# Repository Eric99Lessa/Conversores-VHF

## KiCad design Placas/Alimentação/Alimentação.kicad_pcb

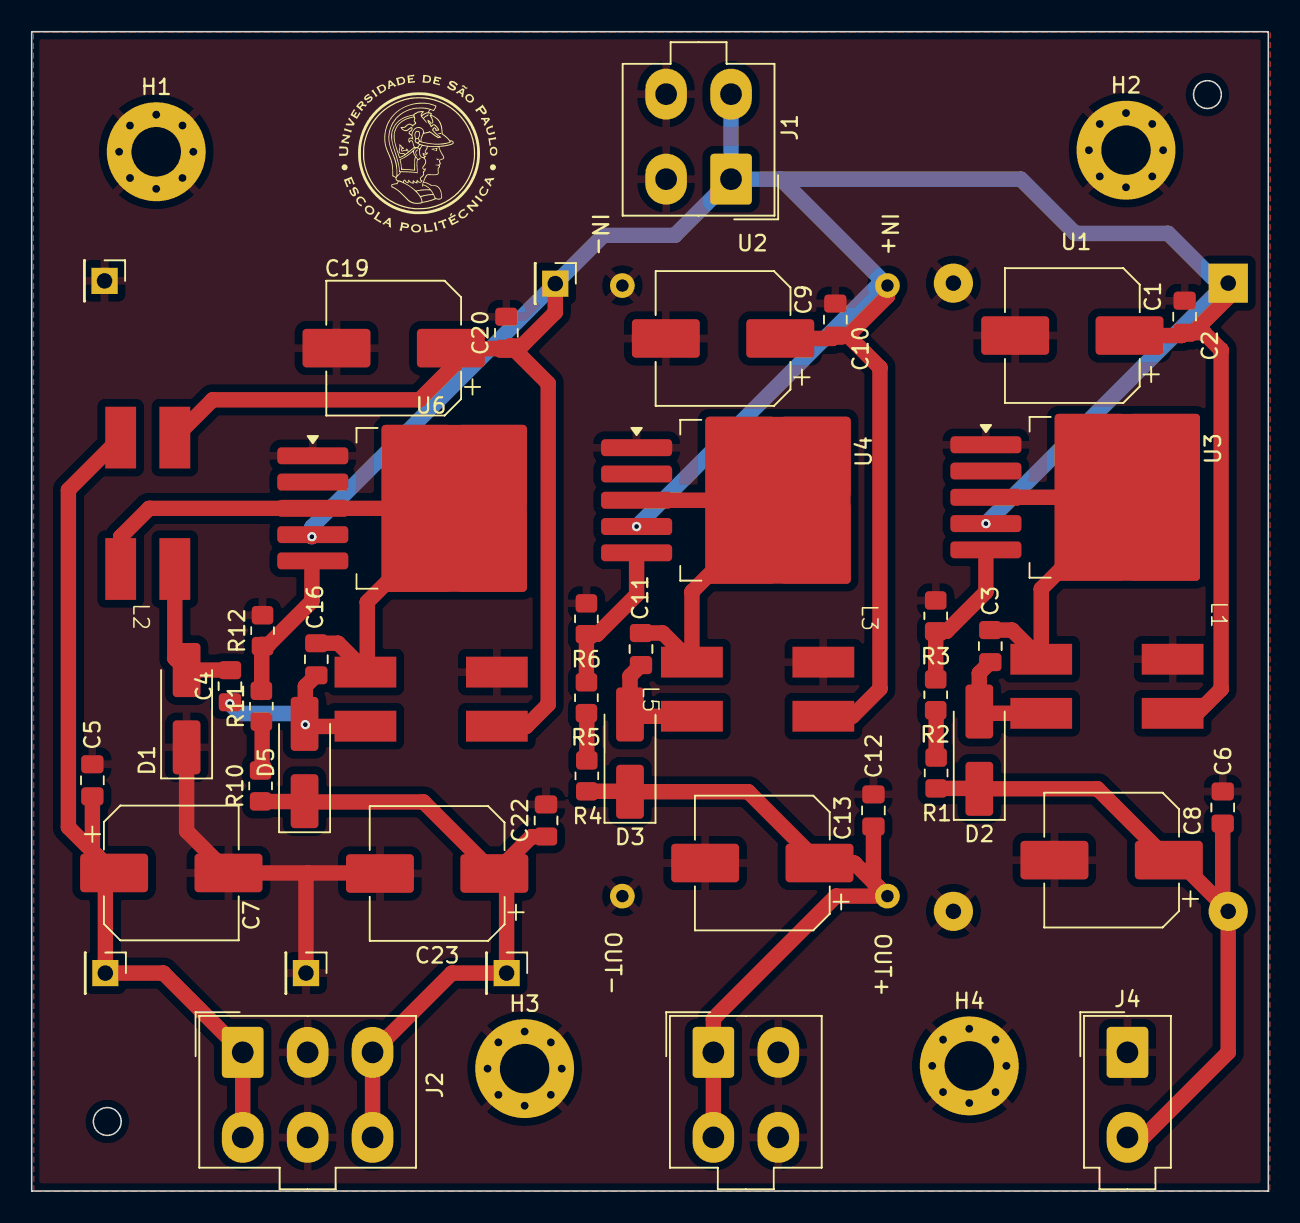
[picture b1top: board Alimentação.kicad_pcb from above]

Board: 2 copper layers, 80.0 x 75.0 mm, 53 parts (0 on the bottom side), 19 nets.

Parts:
C1, C7, C8, C9, C13, C19, C23: 220u; CP_Elec_8x10.5
C2, C5, C6, C10, C12, C20, C22: 1u; C_0805_2012Metric_Pad1.18x1.45mm_HandSolder
C3, C4, C11, C16: 22u; C_0805_2012Metric_Pad1.18x1.45mm_HandSolder
D1, D2, D3, D5: SS14; D_SMA_Handsoldering
H1, H2, H3, H4: MountingHole_Pad; MountingHole_3.2mm_M3_Pad_Via
J1, J3: Conn_02x02_ZigZag; Molex_Mini-Fit_Jr_5566-04A_2x02_P4.20mm_Vertical
J2: Conn_02x03_ZigZag; Molex_Mini-Fit_Jr_5566-06A_2x03_P4.20mm_Vertical
J4: Conn_02x01; Molex_Mini-Fit_Jr_5566-02A_2x01_P4.20mm_Vertical
J13, J14, J15, J16, J17: Conn_01x01_Pin; PinHeader_1x01_P2.54mm_Vertical
L1, L2, L3, L5: MSD1260t; Msd1260t
R1, R2: 1k5; R_0805_2012Metric_Pad1.20x1.40mm_HandSolder
R3, R5, R6, R11, R12: 1k; R_0805_2012Metric_Pad1.20x1.40mm_HandSolder
R4, R10: 10k; R_0805_2012Metric_Pad1.20x1.40mm_HandSolder
U1: YAAJ_DCDC_StepDown_LM2596
U2: Módulo XL6009; XL6009-Module
U3, U4, U6: XL6009; TO-263-5_TabPin3

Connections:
5V: C6.1, C8.1, D2.1 (K), J4.2, R1.1, U1.4 (Vout)
15V: C12.1, C13.1, D3.1 (K), J3.1, J3.3, R4.1, U2.3 (Vout)
+12V: C1.1, C2.1, C9.1, C10.1, C19.1, C20.1, J1.1, J1.3, J13.1, L1.1, L2.1, L3.1, L5.1, U1.1 (Vin), U2.1 (Vin), U3.4 (VIN), U4.4 (VIN), U6.4 (VIN)
+15V_sym: C22.1, C23.1, D5.1 (K), J2.3, J2.6, J17.1, R10.1
-15V_sym: C5.1, C7.1, J2.1, J2.4, J15.1, L2.2
/Conversor 12 to 5V/SEPIC_XL6011/L_out: C3.2, D2.2 (A), L1.4
/Conversor 12 to 5V/SEPIC_XL6011/SW: C3.1, L1.3, U3.3 (SW)
/Conversor 12 to 15V - Simétrico/L_out: C4.1, D5.2 (A), L5.4
/Conversor 12 to 15V - Simétrico/SW: L2.3, L5.3, U6.3 (SW)
/Conversor 12 to 15V/SEPIC_XL6012/L_out: C11.2, D3.2 (A), L3.4
/Conversor 12 to 15V/SEPIC_XL6012/SW: C11.1, L3.3, U4.3 (SW)
GND: C1.2, C2.2, C5.2, C6.2, C7.2, C8.2, C9.2, C10.2, C12.2, C13.2, C19.2, C20.2, C22.2, C23.2, D1.1 (K), H1.1, H2.1, H3.1, H4.1, J1.2, J1.4, J2.2, J2.5, J3.2, J3.4, J4.1, J14.1, J16.1, L1.2, L3.2, L5.2, R3.2, R6.2, R12.2, U1.2 (GND), U1.3 (GND), U2.2 (GND), U2.4 (GND), U3.1 (GND), U4.1 (GND), U6.1 (GND)
unnamed: C4.2, D1.2 (A), L2.4
unnamed: R1.2, R2.1
unnamed: R4.2, R5.1
unnamed: R10.2, R11.1
unnamed: R2.2, R3.1, U3.5 (FB)
unnamed: R5.2, R6.1, U4.5 (FB)
unnamed: R11.2, R12.1, U6.5 (FB)

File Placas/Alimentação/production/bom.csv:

Designator,Footprint,Quantity,Value,LCSC Part #
"C19, C23, C7",CP_Elec_8x10.5,3,220u,
"C20, C22, C5",0805,3,1u,
C4,0805,1,22u,
"D1, D5",D_SMA_Handsoldering,2,SS14,
"J1, J3",Molex_Mini-Fit_Jr_5566-04A_2x02_P4.20mm_Vertical,2,Conn_02x02_ZigZag,
J2,Molex_Mini-Fit_Jr_5566-06A_2x03_P4.20mm_Vertical,1,Conn_02x03_ZigZag,
J4,Molex_Mini-Fit_Jr_5566-02A_2x01_P4.20mm_Vertical,1,Conn_02x01,
"L2, L5",Msd1260t,2,MSD1260t,
R10,0805,1,10k,
"R11, R12",0805,2,1k,
U1,YAAJ_DCDC_StepDown_LM2596,1,YAAJ_DCDC_StepDown_LM2596,
U2,XL6009-Module,1,Módulo XL6009,
U6,TO-263-5_TabPin3,1,XL6009,

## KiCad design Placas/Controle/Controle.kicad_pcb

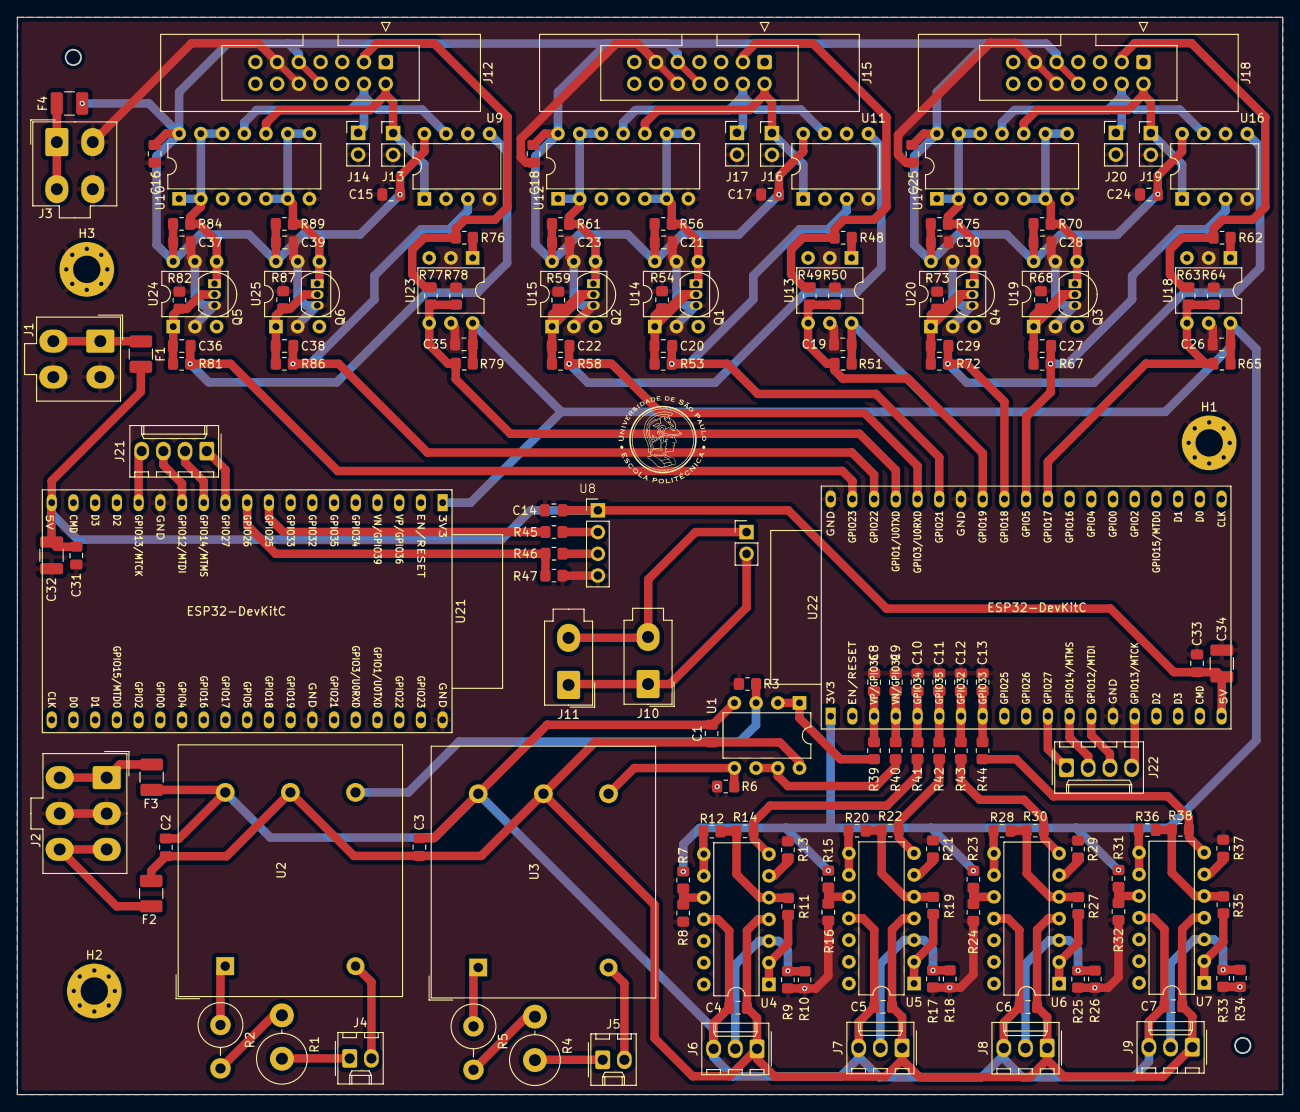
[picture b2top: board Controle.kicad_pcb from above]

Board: 2 copper layers, 148.0 x 126.0 mm, 176 parts (0 on the bottom side), 103 nets.

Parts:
C1, C2, C3, C4, C5, C6, C7, C14, C15, C16, C17, C18, C19, C21, C23, C24, C25, C26, C28, C30, C31, C33, C35, C37, C39: 0,1u; C_0805_2012Metric_Pad1.18x1.45mm_HandSolder
C8, C9, C10, C11, C12, C13: 330n; C_0805_2012Metric_Pad1.18x1.45mm_HandSolder
C20, C22, C27, C29, C36, C38: 6,8n; C_0805_2012Metric_Pad1.18x1.45mm_HandSolder
C32, C34: 10u; C_1210_3225Metric_Pad1.33x2.70mm_HandSolder
F1: 1A; Fuse_1210_3225Metric_Pad1.42x2.65mm_HandSolder
F2, F3: 0,4A; Fuse_1210_3225Metric_Pad1.42x2.65mm_HandSolder
F4: 3A; Fuse_1210_3225Metric_Pad1.42x2.65mm_HandSolder
H1, H2, H3: MountingHole_Pad; MountingHole_3.2mm_M3_Pad_Via
J1, J3: Conn_02x02; Molex_Mini-Fit_Jr_5566-04A_2x02_P4.20mm_Vertical
J2: Conn_02x03; Molex_Mini-Fit_Jr_5566-06A_2x03_P4.20mm_Vertical
J4, J5: Conn_01x02_Pin; Molex_KK-254_AE-6410-02A_1x02_P2.54mm_Vertical
J6, J7, J8, J9: Conn_01x03_Pin; Molex_KK-254_AE-6410-03A_1x03_P2.54mm_Vertical
J10, J11: Conn_01x02_Pin; Molex_Mini-Fit_Jr_5566-02A_2x01_P4.20mm_Vertical
J12, J15, J18: Conn_02x07_Odd_Even; IDC_Header_2x07
J13, J14, J16, J17, J19, J20: Conn_01x02_Pin; PinHeader_1x02_P2.54mm_Vertical
J21, J22: Conn_01x04_Pin; Molex_KK-254_AE-6410-04A_1x04_P2.54mm_Vertical
Q1, Q2, Q3, Q4, Q5, Q6: BC337; TO-92_Inline
R1: 3k3 1W; R_Axial_DIN0614_L14.3mm_D5.7mm_P5.08mm_Vertical
R2: 2k7 1W; R_Axial_DIN0516_L15.5mm_D5.0mm_P5.08mm_Vertical
R3, R6, R9, R10, R17, R18, R25, R26, R33, R34: 100 1/8W; R_0805_2012Metric_Pad1.20x1.40mm_HandSolder
R4: 4k7 2W; R_Axial_DIN0614_L14.3mm_D5.7mm_P5.08mm_Vertical
R5: 3k3 1/2W; R_Axial_DIN0516_L15.5mm_D5.0mm_P5.08mm_Vertical
R7, R8, R11, R12, R14, R15, R16, R19, R20, R22, R23, R24, R27, R28, R30, R31, R32, R35, R36, R38, R46: 10k; R_0805_2012Metric_Pad1.20x1.40mm_HandSolder
R13, R21, R29, R37, R50, R64, R78: 3k3; R_0805_2012Metric_Pad1.20x1.40mm_HandSolder
R39, R40, R41, R42, R43, R44, R51, R56, R61, R65, R70, R75, R79, R84, R89: 1k; R_0805_2012Metric_Pad1.20x1.40mm_HandSolder
R45: 100; R_0805_2012Metric_Pad1.20x1.40mm_HandSolder
R47: 20k; R_0805_2012Metric_Pad1.20x1.40mm_HandSolder
R48, R62, R76: 1k3; R_0805_2012Metric_Pad1.20x1.40mm_HandSolder
R49, R63, R77: 12k; R_0805_2012Metric_Pad1.20x1.40mm_HandSolder
R53, R58, R67, R72, R81, R86: 178; R_0805_2012Metric_Pad1.20x1.40mm_HandSolder
R54, R59, R68, R73, R82, R87: 100k; R_0805_2012Metric_Pad1.20x1.40mm_HandSolder
U1: LM358; DIP-8_W7.62mm
U2, U3: LV25-P; LEM_LV25-P
U4, U5, U6, U7: LM324; DIP-14_W7.62mm
U8: Módulo TJA1050; TJA1050
U9, U11, U16: TL072; DIP-8_W7.62mm
U10, U12, U17: HEF4093B; DIP-14_W7.62mm
U13, U14, U15, U18, U19, U20, U23, U24, U25: H11L1; DIP-6_W7.62mm
U21, U22: ESP32-DevKitC

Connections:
+3.3V: C19.1, C26.1, C35.1, R7.1, R15.1, R23.1, R31.1, R51.1, R65.1, R79.1, U13.6, U18.6, U21.1 (3V3), U22.1 (3V3), U23.6
+5V: C14.1, C31.1, C32.1, C33.1, C34.1, F1.2, U8.1 (VCC), U21.19 (5V), U22.19 (5V)
+15V: C1.1, C2.1, C3.1, C4.1, C5.1, C6.1, C7.1, F2.2, J6.1, J7.1, J8.1, J9.1, U1.8 (V+), U2.5 (V+), U3.5 (V+), U4.4 (V+), U5.4 (V+), U6.4 (V+), U7.4 (V+)
-15V: C1.2, C2.2, C3.2, C4.2, C5.2, C6.2, C7.2, F3.2, J6.3, J7.3, J8.3, J9.3, U1.4 (V-), U2.6 (V-), U3.6 (V-), U4.11 (V-), U5.11 (V-), U6.11 (V-), U7.11 (V-)
/Adequação Sensores/Filtro RC1/unfilt_signal: R40.1, U1.6 (-), U1.7
/Adequação Sensores/Filtro RC2/unfilt_signal: R14.1, R41.1, U4.7
/Adequação Sensores/Filtro RC3/unfilt_signal: R22.1, R42.1, U5.7
/Adequação Sensores/Filtro RC4/unfilt_signal: R30.1, R43.1, U6.7
/Adequação Sensores/Filtro RC5/unfilt_signal: R38.1, R44.1, U7.7
/Adequação Sensores/Filtro RC/unfilt_signal: R39.1, U1.1, U1.2 (-)
/Adequação Sensores/adequacao_sensor_tensao1/output_signal: R6.2, U1.5 (+), U3.4 (M)
/Adequação Sensores/adequacao_sensor_tensao/output_signal: R3.2, U1.3 (+), U2.4 (M)
/Adequação Sinais Driver/Conectores - PWM e erro1/Adequação Sinais - PWM1/in_si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: C20.2, Q1.2 (B), R53.2, R54.1, U14.1
/Adequação Sinais Driver/Conectores - PWM e erro1/Adequação Sinais - PWM/in_sig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: C22.2, Q2.2 (B), R58.2, R59.1, U15.1
/Adequação Sinais Driver/Conectores - PWM e erro1/PWM_BOT_driver: J15.2, J16.1, U11.1, U12.10
/Adequação Sinais Driver/Conectores - PWM e erro1/PWM_BOT_int: Q1.1 (C), R56.2, U12.5, U12.6, U12.8, U12.9, U14.4
/Adequação Sinais Driver/Conectores - PWM e erro1/PWM_TOP_driver: J15.4, J17.1, U11.7, U12.11
/Adequação Sinais Driver/Conectores - PWM e erro1/PWM_TOP_int: Q2.1 (C), R61.2, U12.1, U12.2, U12.12, U12.13, U15.4
/Adequação Sinais Driver/Conectores - PWM e erro1/erro_driver: J15.3, R48.1, R49.2
/Adequação Sinais Driver/Conectores - PWM e erro2/Adequação Sinais - PWM1/in_si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: C27.2, Q3.2 (B), R67.2, R68.1, U19.1
/Adequação Sinais Driver/Conectores - PWM e erro2/Adequação Sinais - PWM/in_sig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: C29.2, Q4.2 (B), R72.2, R73.1, U20.1
/Adequação Sinais Driver/Conectores - PWM e erro2/PWM_BOT_driver: J18.2, J19.1, U16.1, U17.10
/Adequação Sinais Driver/Conectores - PWM e erro2/PWM_BOT_int: Q3.1 (C), R70.2, U17.5, U17.6, U17.8, U17.9, U19.4
/Adequação Sinais Driver/Conectores - PWM e erro2/PWM_TOP_driver: J18.4, J20.1, U16.7, U17.11
/Adequação Sinais Driver/Conectores - PWM e erro2/PWM_TOP_int: Q4.1 (C), R75.2, U17.1, U17.2, U17.12, U17.13, U20.4
/Adequação Sinais Driver/Conectores - PWM e erro2/erro_driver: J18.3, R62.1, R63.2
/Adequação Sinais Driver/Conectores - PWM e erro/Adequação Sinais - PWM1/in_sig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: C38.2, Q6.2 (B), R86.2, R87.1, U25.1
/Adequação Sinais Driver/Conectores - PWM e erro/Adequação Sinais - PWM/in_sign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: C36.2, Q5.2 (B), R81.2, R82.1, U24.1
/Adequação Sinais Driver/Conectores - PWM e erro/PWM_BOT_driver: J12.2, J13.1, U9.1, U10.10
/Adequação Sinais Driver/Conectores - PWM e erro/PWM_BOT_int: Q6.1 (C), R89.2, U10.5, U10.6, U10.8, U10.9, U25.4
/Adequação Sinais Driver/Conectores - PWM e erro/PWM_TOP_driver: J12.4, J14.1, U9.7, U10.11
/Adequação Sinais Driver/Conectores - PWM e erro/PWM_TOP_int: Q5.1 (C), R84.2, U10.1, U10.2, U10.12, U10.13, U24.4
/Adequação Sinais Driver/Conectores - PWM e erro/erro_driver: J12.3, R76.1, R77.2
/Conectores/5V_conn: F1.1, J1.1, J1.3
/Conectores/+15V_sym_conn: F2.1, J2.3, J2.6
/Conectores/-15V_sym_conn: F3.1, J2.1, J2.4
/Conectores/Vdrive_conn: F4.1, J3.1, J3.3
/I_read_L1: C10.1, R41.2, U22.5 (VDET_1/GPIO34/ADC1_CH6)
/I_read_L2: C11.1, R42.2, U22.6 (VDET_2/GPIO35/ADC1_CH7)
/I_read_L3: C12.1, R43.2, U22.7 (32K_XP/GPIO32/ADC1_CH4)
/I_read_out: C13.1, R44.2, U22.8 (32K_XN/GPIO33/ADC1_CH5)
/Microcontrolados e CAN/CANH: J10.2, J11.2, U8.5 (CANH)
/Microcontrolados e CAN/CANL: J10.1, J11.1, U8.6 (CANL)
/Microcontrolados e CAN/CAN_RX_esp: R46.2, R47.1, U21.10 (DAC_2/ADC2_CH9/GPIO26)
/Microcontrolados e CAN/CAN_RX_trans: R46.1, U8.3 (RX)
/Microcontrolados e CAN/CAN_TX_esp: R45.2, U21.9 (DAC_1/ADC2_CH8/GPIO25)
/Microcontrolados e CAN/CAN_TX_trans: R45.1, U8.2 (TX)
/Microcontrolados e CAN/CS_1: J22.1, U22.11 (ADC2_CH7/GPIO27)
/Microcontrolados e CAN/CS_2: J21.1, U21.11 (ADC2_CH7/GPIO27)
/Microcontrolados e CAN/MISO_1: J22.3, U22.13 (MTDI/GPIO12/ADC2_CH5)
/Microcontrolados e CAN/MISO_2: J21.3, U21.13 (MTDI/GPIO12/ADC2_CH5)
/Microcontrolados e CAN/MOSI_1: J22.4, U22.15 (MTCK/GPIO13/ADC2_CH4)
/Microcontrolados e CAN/MOSI_2: J21.4, U21.15 (MTCK/GPIO13/ADC2_CH4)
/Microcontrolados e CAN/SCK_1: J22.2, U22.12 (MTMS/GPIO14/ADC2_CH6)
/Microcontrolados e CAN/SCK_2: J21.2, U21.12 (MTMS/GPIO14/ADC2_CH6)
/PWM_BOT_1: C38.1, R86.1, U9.3 (+), U22.36 (GPIO22)
/PWM_BOT_2: C20.1, R53.1, U11.3 (+), U22.33 (GPIO21)
/PWM_BOT_3: C29.1, R72.1, U16.5 (+), U22.30 (GPIO18)
/PWM_TOP_1: C36.1, R81.1, U9.5 (+), U22.37 (GPIO23)
/PWM_TOP_2: C22.1, R58.1, U11.5 (+), U22.34 (U0RXD/GPIO3)
/PWM_TOP_3: C27.1, R67.1, U16.3 (+), U22.29 (GPIO5)
/V_read_in: C8.1, R39.2, U22.3 (SENSOR_VP/GPIO36/ADC1_CH0)
/V_read_out: C9.1, R40.2, U22.4 (SENSOR_VN/GPIO39/ADC1_CH3)
/err_1: R77.1, R78.2, R79.2, U22.35 (U0TXD/GPIO1), U23.4
/err_2: R49.1, R50.2, R51.2, U13.4, U22.31 (GPIO19)
/err_3: R63.1, R64.2, R65.2, U18.4, U22.28 (GPIO17)
GND: C8.2, C9.2, C10.2, C11.2, C12.2, C13.2, C14.2, C15.2, C16.2, C17.2, C18.2, C19.2, C21.2, C23.2, C24.2, C25.2, C26.2, C28.2, C30.2, C31.2, C32.2, C33.2, C34.2, C35.2, C37.2, C39.2, H1.1, H2.1, H3.1, J1.2, J1.4, J2.2, J2.5, J3.2, J3.4, J12.10, J12.11, J13.2, J14.2, J15.10, J15.11, J16.2, J17.2, J18.10, J18.11, J19.2, J20.2, Q1.3 (E), Q2.3 (E), Q3.3 (E), Q4.3 (E), Q5.3 (E), Q6.3 (E), R3.1, R6.1, R8.2, R9.1, R10.1, R13.2, R16.2, R17.1, R18.1, R21.2, R24.2, R25.1, R26.1, R29.2, R32.2, R33.1, R34.1, R37.2, R47.2, R50.1, R54.2, R59.2, R64.1, R68.2, R73.2, R78.1, R82.2, R87.2, U8.4 (GND), U9.2 (-), U9.4 (V-), U9.6 (-), U10.7 (GND), U11.2 (-), U11.4 (V-), U11.6 (-), U12.7 (GND), U13.2, U13.5, U14.2, U14.5, U15.2, U15.5, U16.2 (-), U16.4 (V-), U16.6 (-), U17.7 (GND), U18.2, U18.5, U19.2, U19.5, U20.2, U20.5, U21.14 (GND), U21.32 (GND), U21.38 (GND), U22.14 (GND), U22.32 (GND), U22.38 (GND), U23.2, U23.5, U24.2, U24.5, U25.2, U25.5
unnamed: J4.1, R1.1
unnamed: J4.2, U2.3 (HV-)
unnamed: J5.1, R4.1
unnamed: J5.2, U3.3 (HV-)
unnamed: J6.2, R9.2, R10.2, U4.3 (+)
unnamed: J7.2, R17.2, R18.2, U5.3 (+)
unnamed: J8.2, R25.2, R26.2, U6.3 (+)
unnamed: J9.2, R33.2, R34.2, U7.3 (+)
unnamed: R1.2, R2.2
unnamed: R4.2, R5.2
unnamed: R48.2, U13.1
unnamed: R62.2, U18.1
unnamed: R76.2, U23.1
unnamed: R2.1, U2.1 (HV+)
unnamed: R5.1, U3.1 (HV+)
unnamed: R11.2, U4.1, U4.2 (-)
unnamed: R11.1, R12.1, R14.2, U4.5 (+)
unnamed: R13.1, U4.6 (-)
unnamed: R7.2, R8.1, U4.10 (+)
unnamed: R12.2, U4.8, U4.9 (-)
unnamed: R19.2, U5.1, U5.2 (-)
unnamed: R19.1, R20.1, R22.2, U5.5 (+)
unnamed: R21.1, U5.6 (-)
unnamed: R15.2, R16.1, U5.10 (+)
unnamed: R20.2, U5.8, U5.9 (-)
unnamed: R27.2, U6.1, U6.2 (-)
unnamed: R27.1, R28.1, R30.2, U6.5 (+)
unnamed: R29.1, U6.6 (-)
unnamed: R23.2, R24.1, U6.10 (+)
unnamed: R28.2, U6.8, U6.9 (-)
unnamed: R35.2, U7.1, U7.2 (-)
unnamed: R35.1, R36.1, R38.2, U7.5 (+)
unnamed: R37.1, U7.6 (-)
unnamed: R31.2, R32.1, U7.10 (+)
unnamed: R36.2, U7.8, U7.9 (-)
Vdrive: C15.1, C16.1, C17.1, C18.1, C21.1, C23.1, C24.1, C25.1, C28.1, C30.1, C37.1, C39.1, F4.2, J12.8, J12.9, J15.8, J15.9, J18.8, J18.9, R56.1, R61.1, R70.1, R75.1, R84.1, R89.1, U9.8 (V+), U10.14 (VCC), U11.8 (V+), U12.14 (VCC), U14.6, U15.6, U16.8 (V+), U17.14 (VCC), U19.6, U20.6, U24.6, U25.6

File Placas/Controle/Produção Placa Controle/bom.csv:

Designator,Footprint,Quantity,Value,LCSC Part #
"C1, C14, C15, C16, C17, C18, C19, C2, C21, C23, C24, C25, C26, C28, C3, C30, C31, C33, C35, C37, C39, C4, C5, C6, C7",0805,25,"0,1u",
"C10, C11, C12, C13, C8, C9",0805,6,330n,
"C20, C22, C27, C29, C36, C38",0805,6,"6,8n",
"C32, C34",1210,2,10u,
F1,1210,1,1A,
"F2, F3",1210,2,"0,4A",
F4,1210,1,3A,
"J1, J3",Molex_Mini-Fit_Jr_5566-04A_2x02_P4.20mm_Vertical,2,Conn_02x02,
"J10, J11",Molex_Mini-Fit_Jr_5566-02A_2x01_P4.20mm_Vertical,2,Conn_01x02_Pin,
"J12, J15, J18",IDC_Header_2x07,3,Conn_02x07_Odd_Even,
"J13, J14, J16, J17, J19, J20",PinHeader_1x02_P2.54mm_Vertical,6,Conn_01x02_Pin,
J2,Molex_Mini-Fit_Jr_5566-06A_2x03_P4.20mm_Vertical,1,Conn_02x03,
"J21, J22",Molex_KK-254_AE-6410-04A_1x04_P2.54mm_Vertical,2,Conn_01x04_Pin,
"J4, J5",Molex_KK-254_AE-6410-02A_1x02_P2.54mm_Vertical,2,Conn_01x02_Pin,
"J6, J7, J8, J9",Molex_KK-254_AE-6410-03A_1x03_P2.54mm_Vertical,4,Conn_01x03_Pin,
R1,R_Axial_DIN0614_L14.3mm_D5.7mm_P5.08mm_Vertical,1,3k3 1W,
"R10, R17, R18, R25, R26, R3, R33, R34, R6, R9",0805,10,91 1/8W,
"R11, R12, R14, R15, R16, R19, R20, R22, R23, R24, R27, R28, R30, R31, R32, R35, R36, R38, R46, R7, R8",0805,21,10k,
"R13, R21, R29, R37",0805,4,3k3,
R2,R_Axial_DIN0516_L15.5mm_D5.0mm_P5.08mm_Vertical,1,2k7 1W,
"R39, R40, R41, R42, R43, R44, R51, R56, R61, R65, R70, R75, R79, R84, R89",0805,15,1k,
R4,R_Axial_DIN0614_L14.3mm_D5.7mm_P5.08mm_Vertical,1,4k7 2W,
R45,0805,1,100,
R47,0805,1,20k,
"R48, R62, R76",0805,3,1k3,
"R49, R63, R77",0805,3,39k,
R5,R_Axial_DIN0516_L15.5mm_D5.0mm_P5.08mm_Vertical,1,3k3 1/2W,
"R50, R64, R78",0805,3,11k,
"R53, R58, R67, R72, R81, R86",0805,6,180,
"R54, R59, R68, R73, R82, R87",0805,6,100k,
U1,DIP-8_W7.62mm,1,LM358,
"U10, U12, U17",DIP-14_W7.62mm,3,HEF4093B,
"U11, U16, U9",DIP-8_W7.62mm,3,TL072,
"U13, U14, U15, U18, U19, U20, U23, U24, U25",DIP-6_W7.62mm,9,H11L1,
"U2, U3",LEM_LV25-P,2,LV25-P,
"U21, U22",ESP32-DevKitC,2,ESP32-DevKitC,
"U4, U5, U6, U7",DIP-14_W7.62mm,4,LM324,
U8,TJA1050,1,TJA1050,

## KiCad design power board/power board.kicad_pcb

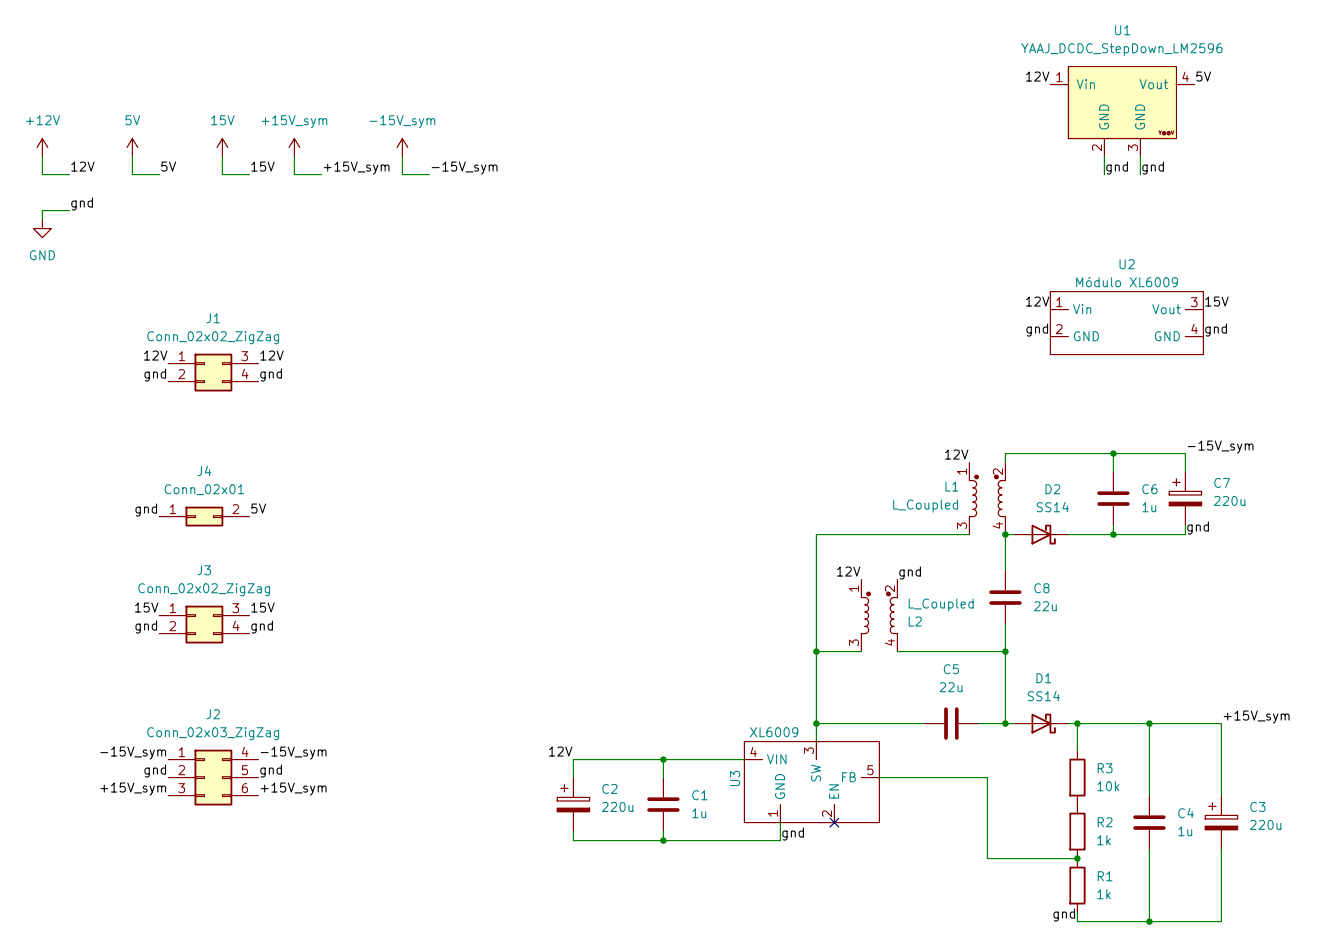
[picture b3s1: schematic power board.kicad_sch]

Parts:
C1, C4, C6: 1u; C_0805_2012Metric_Pad1.18x1.45mm_HandSolder
C2, C3, C7: 220u; CP_Elec_10x10.5
C5, C8: 22u; C_0805_2012Metric_Pad1.18x1.45mm_HandSolder
D1, D2: SS14; D_0805_2012Metric_Pad1.15x1.40mm_HandSolder
J1, J3: Conn_02x02_ZigZag; Molex_Mini-Fit_Jr_5566-04A_2x02_P4.20mm_Vertical
J2: Conn_02x03_ZigZag; Molex_Mini-Fit_Jr_5566-06A_2x03_P4.20mm_Vertical
J4: Conn_02x01; Molex_Mini-Fit_Jr_5566-02A_2x01_P4.20mm_Vertical
L1, L2: L_Coupled; Msd1260t
R1, R2: 1k; R_0805_2012Metric_Pad1.20x1.40mm_HandSolder
R3: 10k; R_0805_2012Metric_Pad1.20x1.40mm_HandSolder
U1: YAAJ_DCDC_StepDown_LM2596
U2: Módulo XL6009; XL6009-Module
U3: XL6009; TO-263-5_TabPin3

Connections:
5V: J4.2, U1.4 (Vout)
15V: J3.1, J3.3, U2.3 (Vout)
+12V: C1.1, C2.1, J1.1, J1.3, L1.1, L2.1, U1.1 (Vin), U2.1 (Vin), U3.4 (VIN)
+15V_sym: C3.1, C4.1, D1.1 (K), J2.3, J2.6, R3.1
-15V_sym: C6.1, C7.1, J2.1, J2.4, L1.2
GND: C1.2, C2.2, C3.2, C4.2, C6.2, C7.2, D2.1 (K), J1.2, J1.4, J2.2, J2.5, J3.2, J3.4, J4.1, L2.2, R1.2, U1.2 (GND), U1.3 (GND), U2.2 (GND), U2.4 (GND), U3.1 (GND)
unnamed: C5.2, C8.1, D1.2 (A), L2.4
unnamed: C8.2, D2.2 (A), L1.4
unnamed: R2.1, R3.2
unnamed: R1.1, R2.2, U3.5 (FB)
unnamed: C5.1, L1.3, L2.3, U3.3 (SW)

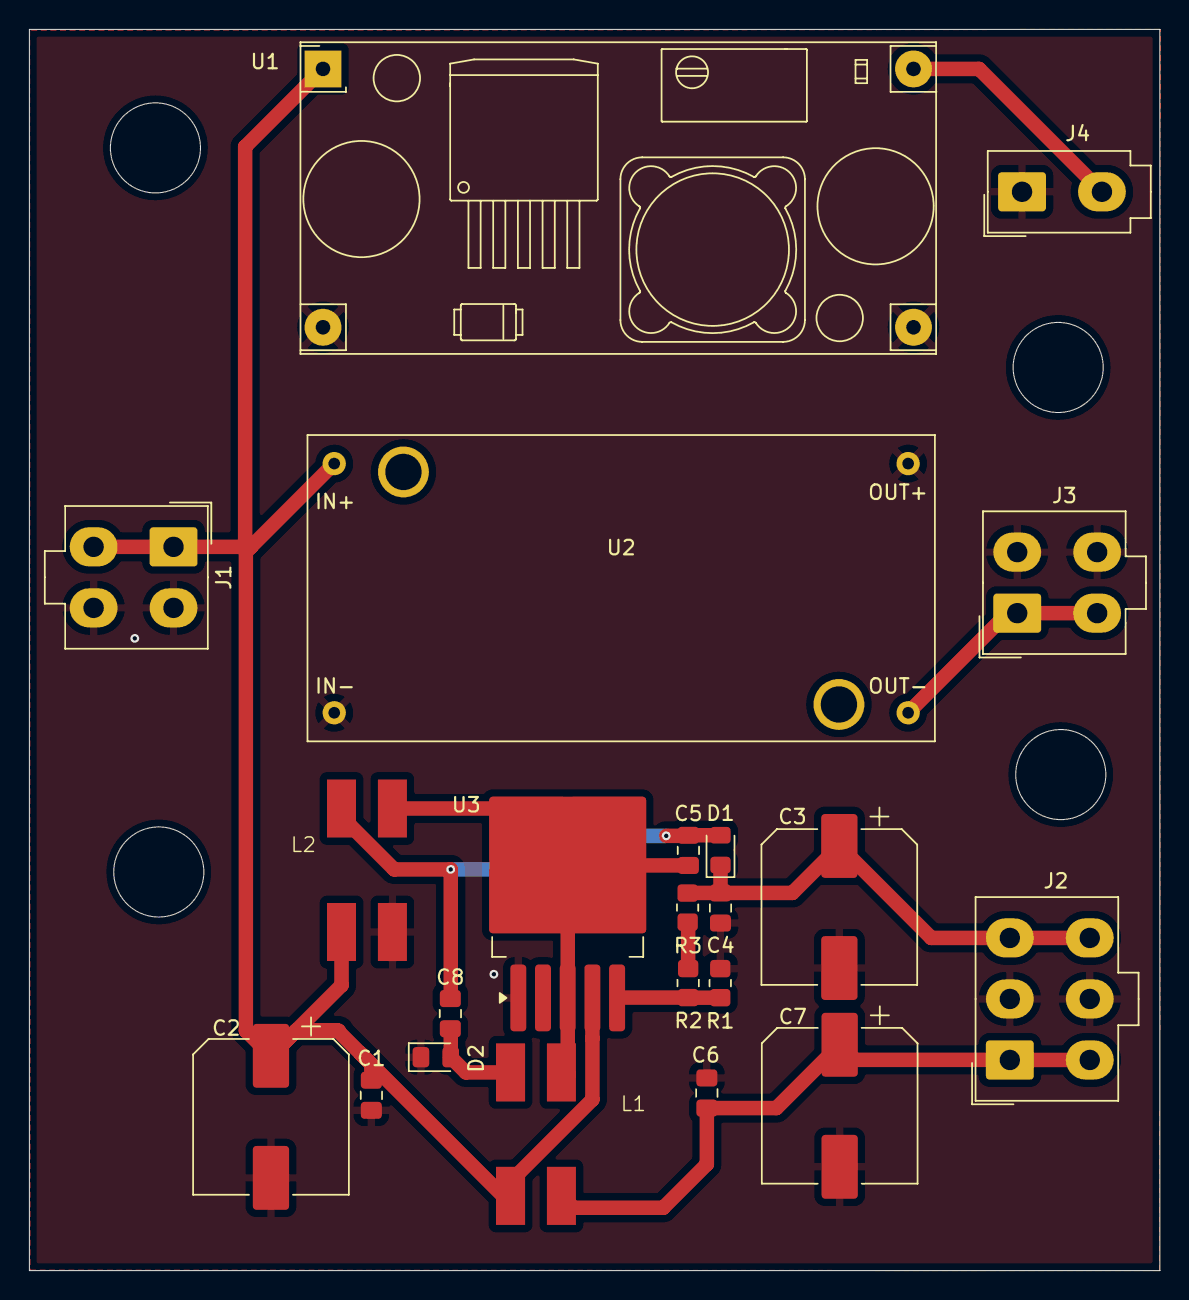
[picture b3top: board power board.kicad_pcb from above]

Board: 2 copper layers, 77.8 x 85.4 mm, 22 parts (0 on the bottom side), 11 nets.
